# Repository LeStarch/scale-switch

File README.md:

# ScaleAV Switch

Switch supporting Scale 17x.

Make sure to install dependencies:
```
pip install platformio
git submodule update --init --recursive
```

Build and Upload:
```
platformio run --target upload
```

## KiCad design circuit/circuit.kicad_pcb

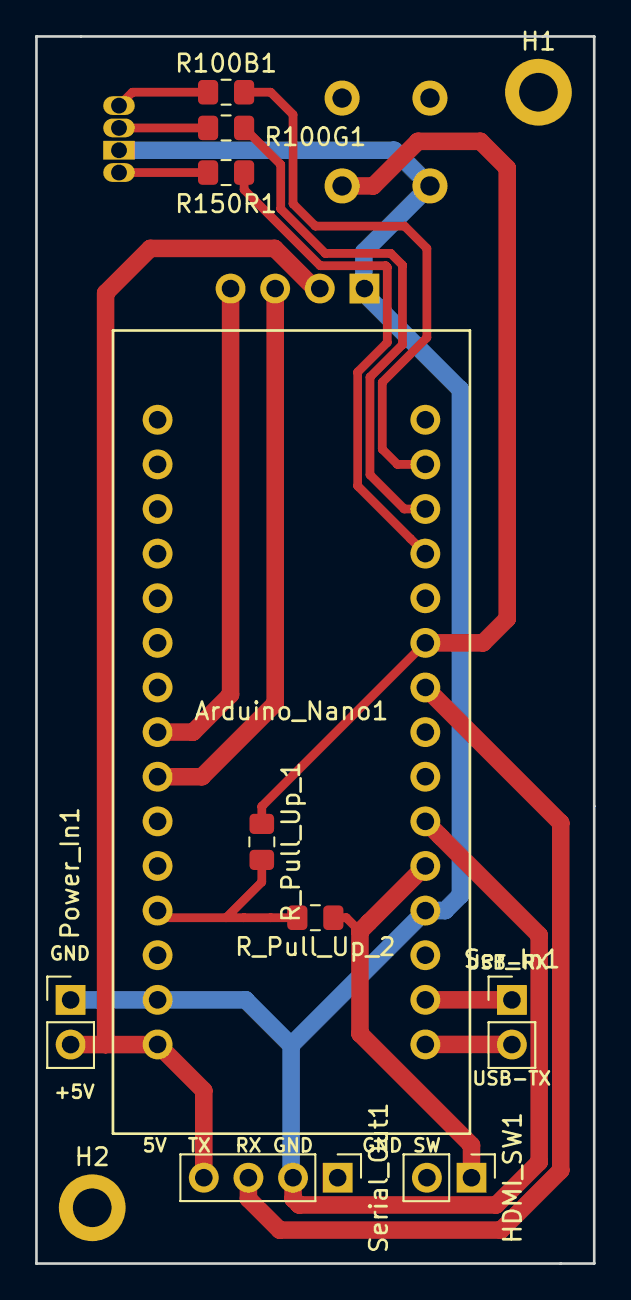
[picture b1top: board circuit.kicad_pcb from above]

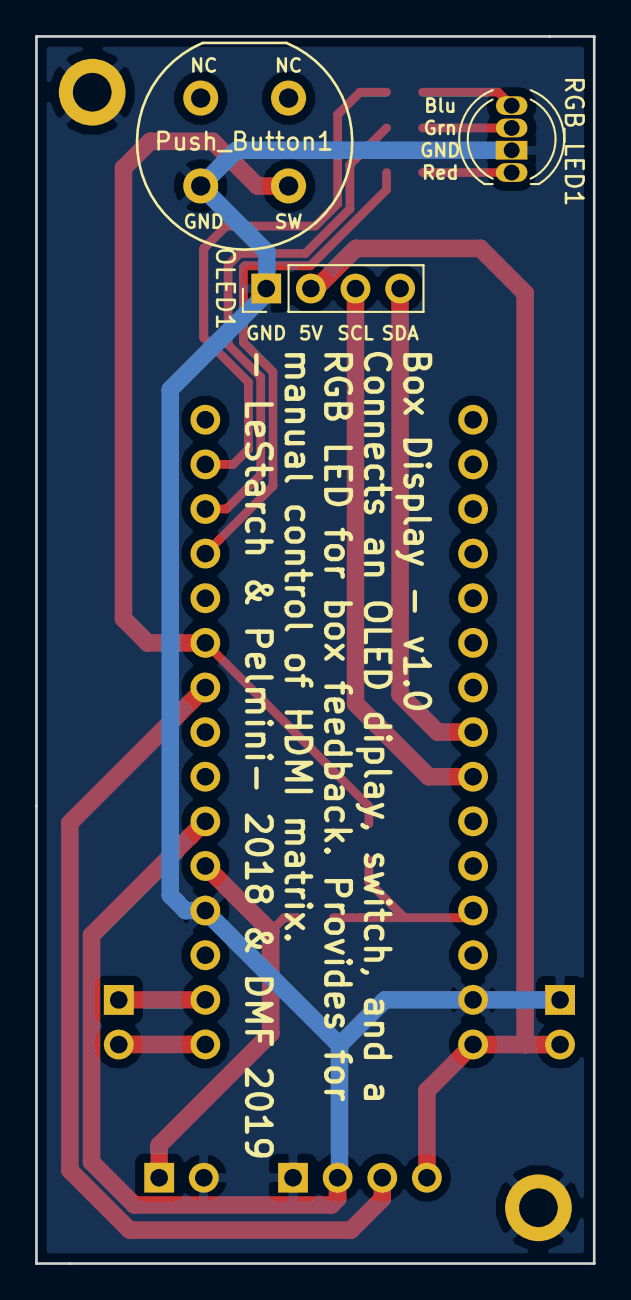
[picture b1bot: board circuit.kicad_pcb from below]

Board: 2 copper layers, 31.8 x 69.8 mm, 15 parts (3 on the bottom side), 17 nets.

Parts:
Arduino_Nano1: Arduino_Nano; Nano
H1, H2: MountingHole_Pad; MountingHole_2.2mm_M2_DIN965_Pad
HDMI_SW1: HDMI Switch; PinHeader_1x02_P2.54mm_Vertical
OLED1: I2C Out; PinHeader_1x04_P2.54mm_Vertical
Power_In1: Power In; PinHeader_1x02_P2.54mm_Vertical
Push_Button1: SW_SPST; Push_E-Switch_KS01Q01
R100B1, R100G1: R100; R_0805_2012Metric_Pad1.15x1.40mm_HandSolder
R150R1: R150; R_0805_2012Metric_Pad1.15x1.40mm_HandSolder
RGB_LED1: LED_C2RGB; LED_D5.0mm-RGPC
R_Pull_Up_1, R_Pull_Up_2: R; R_0805_2012Metric_Pad1.15x1.40mm_HandSolder
Ser_In1: Serial In; PinHeader_1x02_P2.54mm_Vertical
Serial_Out1: Serial Out; PinHeader_1x04_P2.54mm_Vertical

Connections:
+5V: Arduino_Nano1.Vin, OLED1.2, Power_In1.2, Serial_Out1.4
GND: Arduino_Nano1.GND, H1.1, H2.1, HDMI_SW1.2, OLED1.1, Power_In1.1, Push_Button1.2, RGB_LED1.2, Serial_Out1.1
unnamed: Arduino_Nano1.5V, R_Pull_Up_1.2, R_Pull_Up_2.2
unnamed: Arduino_Nano1.A4, OLED1.4
unnamed: Arduino_Nano1.A5, OLED1.3
unnamed: Arduino_Nano1.D2, HDMI_SW1.1, R_Pull_Up_2.1
unnamed: Arduino_Nano1.D3, Serial_Out1.2
unnamed: Arduino_Nano1.D6, Serial_Out1.3
unnamed: Arduino_Nano1.D7, Push_Button1.1, R_Pull_Up_1.1
unnamed: Arduino_Nano1.D9, R150R1.2
unnamed: Arduino_Nano1.D10, R100G1.2
unnamed: Arduino_Nano1.D11, R100B1.2
unnamed: Arduino_Nano1.RX0, Ser_In1.1
unnamed: Arduino_Nano1.TX1, Ser_In1.2
unnamed: R100B1.1, RGB_LED1.4
unnamed: R100G1.1, RGB_LED1.3
unnamed: R150R1.1, RGB_LED1.1

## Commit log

2018-10-22 mstarch: initial scale switch implementation
2018-11-05 lestarch: adding pull up; falling interrupt trigger
2018-11-05 lestarch: adding KiCad circuit for OLED display and HDMI connections
2018-11-10 lestarch: basic button and LED13 framework; eclipse files
2018-11-10 lestarch: adding RGB indicator
2018-11-10 lestarch: adding adafruit libraries as submodules
2018-11-10 lestarch: updating README.md
2018-11-24 lestarch: memory optimized working LED, RGBLED, OLED
2018-12-03 Redid the I2Cwires, made Aruduino holes bigger, corrected annotations
2019-01-06 Added Mounting holes
2019-01-06 fix short
2019-01-20 lestarch: adding full-functional prototype
2019-02-07 lestarch: refactoring pass-through
2019-02-08 lestarch: working tested serial pass through
2020-02-24 lestarch: updating output to slot 2
2020-02-27 lestarch: signage and podium indication
2020-02-29 lestarch: fixing command collision
2020-02-29 lestarch: response handling and not shitty code
2020-03-08 lestarch: adding firmware version; preventing LED on startup
2020-03-08 lestarch: message cooldown
2020-03-08 lestarch: autogenerating src/version.cpp
2020-03-08 lestarch: fixing firmware bug, adding cleanliness
